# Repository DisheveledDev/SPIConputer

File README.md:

# SPIConputer (working title)

> A retro computer whose system bus is SPI. Every peripheral is an
> autonomous node with its own microcontroller; the main CPU sends it a
> command and the node carries it out without further CPU involvement.

## Status

Design phase. Nothing is built yet. This README is the living design
document: decisions go in the [Decision log](#decision-log), unresolved
items live in [Open questions](#open-questions).

## Concept

- **Bus = SPI.** SCK, MOSI and MISO are shared across all nodes; each
  node gets its own chip-select (SS) line from the main CPU.
- **Autonomous peripherals.** Each node (video, storage, IO, sound,
  console) has its own MCU (ATmega328 or similar). The main CPU issues
  high-level commands ("draw this sprite", "read sector N", "play this
  note") and moves on. Nodes report completion asynchronously.
- **C64 form factor.** The board fits inside a Commodore 64 shell,
  reusing its keyboard and (ideally) its port cutouts.

## Architecture overview

```
                                  +----------------------+
                                  |  MAIN CPU (master)   |
                                  |  MCU: TBD            |
                                  +--+--+--+--+--+--+----+
                                     |  |  |  |  |  |
        Bus: SCK + MOSI + MISO shared; one SS per node; IRQ per node (TBD)
                                     |  |  |  |  |  |
        +----------------------------+  |  |  |  |  +--------------------------+
        |                               |  |  |  |                             |
  +-----+--------+              +-------+  |  |  +-------+             +-------+--------+
  | VIDEO NODE   |              | IO NODE |  |  | STORAGE |             | SOUND NODE     |
  | ATmega2560   |              | ATmega  |  |  | NODE    |             | ATmega328 (TBD)|
  +-----+--------+              +---+-----+  |  +----+----+             +-------+--------+
        |                           |        |       |                         |
  2nd SPI -> Flash           C64 keyboard    |   SD card (SPI)           Audio out (TBD)
  (tile/glyph data)          Joystick x2     |
        |                           |        |
       VGA (DB15)                   |        |
                                    |   +----+--------+
                                    |   | CONSOLE NODE |
                                    |   | RS232 / TBD  |
                                    |   +-------------+
                                    |
                          +---------+---------+
                          | EXPANSION (SDI)   |
                          | bus passthrough   |
                          +-------------------+
```

## System bus

### Signals

| Signal | Direction | Notes |
| ------ | --------- | ----- |
| SCK    | master -> all | Bus clock |
| MOSI   | master -> all | Master out, slave in |
| MISO   | all -> master | Shared; slaves tri-state when not selected |
| SS_n   | master -> one node each | Dedicated chip-select per node |
| IRQ_n  | node -> master | Async completion signal (scheme TBD) |

### Protocol (proposal, unverified)

- Every transaction: master asserts the node's SS, sends a 1-byte
  command, an optional length byte, then payload. The slave responds
  with status byte(s) in the same transfer.
- Each node exposes a small **register map**: writing a command
  register starts an autonomous operation; a status register reports
  idle/busy/done/error; data registers move payloads.
- Completion: node asserts IRQ_n when done (or master polls status).
  See [Open questions](#open-questions).

### Timing and electrical gotchas

- **Slave clock limit:** on classic AVRs, SPI *slave* mode tops out at
  Fosc/4 (4 MHz at 16 MHz Fosc) even though *master* mode can run at
  Fosc/2 (8 MHz). The bus clock is therefore realistically **4 MHz**
  unless a node runs a faster crystal or a different SPI peripheral.
- **Shared MISO:** AVR SPI hardware tri-states MISO while SS is
  deasserted, which is what makes the shared bus work. Firmware must
  keep the SPI peripheral in slave mode; don't reuse MISO as a GPIO
  output.
- **Master SS pin:** in AVR SPI master mode the SS pin must be an
  output (or held high) or the master's own SPI can drop into slave
  mode on a false edge.
- Keep traces short; bus speed is modest but the bus crosses multiple
  boards/connectors.

## Nodes

### Main CPU (master)

- MCU: **TBD**. Candidates: ATmega2560 (fits the all-AVR theme and has
  enough pins for per-node SS + IRQ), or something bigger.
- Owns the bus, dispatches commands, runs the OS/shell/BASIC.
- Needs enough GPIO for: one SS per node, one IRQ per node, any
  console-side RS232 if not handled by a node.

### Video node

- MCU: **ATmega2560-16AU** (specified).
- Output: **VGA via DB15** (rear panel).
- Rendering: **text/sprite system**. Tile map and sprite list live in
  SRAM; tile/glyph bitmaps live in an external **SPI flash** on a
  *second* SPI bus (separate from the system bus).
- Firmware renders scanlines, not a CPU-driven framebuffer.

**Timing budget** (this constrains every video decision):

- Pixel clock comes from an AVR shift register (SPI/USART in master
  mode) = Fosc/2 = **8 MHz** at 16 MHz Fosc.
- One VGA line (31.78 µs) = ~254 pixel clocks at 8 MHz, so visible
  width is roughly **160-250 px** at 1 bit per pixel, packed 8 px per
  byte (~25-30 bytes per line, ~1 µs per byte shifted out).
- Flash reads also max out at ~1 byte/µs (8 MHz SPI). Fetching tile
  data on the fly leaves zero slack, so glyphs/tile rows must be
  **cached into SRAM during blanking** (8 KB SRAM on the 2560).
- Resolutions, colour depth (e.g. 3-bit RGB via 3 pins vs. resistor
  DAC) and sprite count are all [open questions](#open-questions).

### IO node

- MCU: ATmega328 or similar.
- Drives the **C64 keyboard** (8x8 matrix, needs 16 GPIOs + pull-ups)
  via the internal connector, and two **DB9 joystick ports**
  (Atari/C64 standard: 4 directions + fire, active-low, pulled high).
- Scans/debounces locally; the main CPU reads key/joystick *events*,
  not raw matrix state.

### Storage node

- MCU: ATmega328 or similar.
- **SD card in SPI mode** (rear panel slot).
- Exposes block read/write; FAT layer either here or on the main CPU.
- Gotcha: SD cards are **3.3 V logic** — the node needs a 3.3 V rail
  (LDO) and level shifting on MOSI/SCK/SS (MISO can usually feed 5 V
  inputs directly through a divider). Classic AVRs are 5 V parts.

### Console node

- **RS232** serial console (rear panel, DB9).
- Open: true RS232 levels (needs a MAX232-style transceiver) vs. TTL
  serial vs. USB (FTDI/CH340). This node may end up merged into the IO
  node.

### Sound node

- MCU: ATmega328 or similar (TBD).
- Receives note/effect commands and generates audio autonomously;
  output via PWM + RC filter, then amp/jack (TBD).
- Open: chiptune-style synth, sample playback, or a SID-inspired voice
  set.

### Expansion (SDI)

- Rear-panel expansion connector. Intended as a passthrough of the
  system bus (SCK/MOSI/MISO + an SS/IRQ pair + power) so new nodes can
  hang off the bus.
- **"SDI" needs defining** — see [Open questions](#open-questions).

## Connectors

| Connector | Location | Standard / notes |
| --------- | -------- | ---------------- |
| VGA       | rear     | DB15, driven by video node |
| Console   | rear     | DB9 RS232 (or USB) — TBD |
| Expansion | rear     | SDI — bus passthrough, pinout TBD |
| SD card   | rear/side | microSD slot, SPI mode |
| Joystick x2 | rear/side | DB9, Atari/C64 standard |
| Keyboard  | internal | C64 keyboard connector, matrix scan by IO node |
| Power     | rear     | 5 V barrel jack — TBD |

## Form factor

- Board must fit a **C64 shell**; port cutouts should line up with the
  case openings. Open: which C64 revision (breadbin vs. 64C) — they
  have different keyboard connectors and cutouts.

## Power

- Single **5 V** rail for all nodes; local 3.3 V LDO on the storage
  node (and anywhere else 3.3 V logic appears). Total draw is small
  (a handful of AVRs + flash + SD), but budget should be verified once
  nodes are prototyped.

## Firmware conventions (proposed)

- Every node: **command loop** — SPI slave ISR receives command frames,
  main loop executes the current task, sets status, raises IRQ.
- Shared node firmware skeleton/library would avoid re-implementing the
  bus layer per node (TBD once toolchain is chosen).
- Each board exposes an **ICSP/ISP header** for initial programming
  and bootloader flashing.

## Development tooling

TBD. Candidates: avr-gcc + avrdude directly, PlatformIO, or Arduino
CLI. Decide in the [Decision log](#decision-log) and document the
canonical build/flash commands here once real code exists.

## Decision log

| # | Decision | Rationale | Date |
| - | -------- | --------- | ---- |
|   | *(none yet)* |  |  |

## Open questions

1. **Main CPU** — which MCU drives the bus and runs the OS?
2. **Bus protocol** — exact command framing; register-map layout per
   node; IRQ scheme (one line per node vs. shared open-collector).
3. **Video modes** — target resolution(s), colour depth, sprite count,
   tile cache strategy within the 8 MHz pixel-clock budget.
4. **SDI definition** — what exactly does the expansion connector
   carry, and what can plug into it?
5. **Sound architecture** — synth vs. samples, voice count, output
   stage (amp, jack on case?).
6. **Console** — true RS232 levels, TTL, or USB?
7. **C64 case revision** — breadbin or 64C (keyboard connector,
   cutouts, mounting holes differ).
8. **Toolchain** — avr-gcc / PlatformIO / Arduino, and the flash
   workflow for each node.
9. **Firmware framework** — shared bus-layer library across nodes, or
   per-node implementations?

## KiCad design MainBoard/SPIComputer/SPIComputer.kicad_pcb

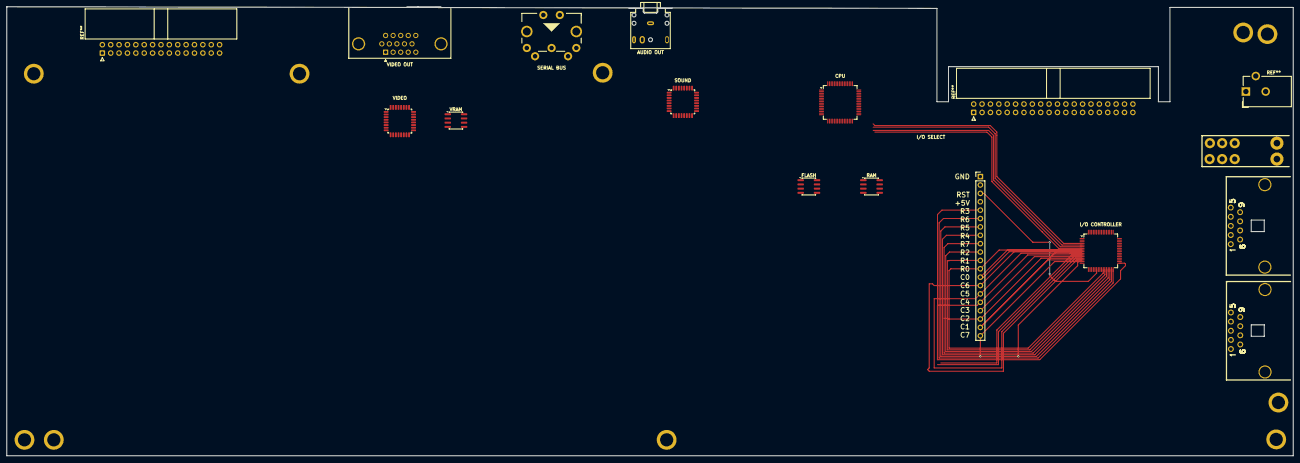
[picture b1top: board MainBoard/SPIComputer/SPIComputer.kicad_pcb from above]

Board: 2 copper layers, 390.0 x 136.1 mm, 14 parts (0 on the bottom side), 2 nets.

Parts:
AUDIO OUT: Jack_3.5mm; Jack_3.5mm_CUI_SJ1-3524N_Horizontal
CN8, CN9: JOYPORT_DB9
CPU: AVR128DB64-I-PT
FLASH: SOIC-8_3.9x4.9mm_P1.27mm
HOLE4: (no value)
I/O CONTROLLER: AVR128DB64-I-PT
RAM: SOIC-8_3.9x4.9mm_P1.27mm
SERIAL BUS: DIN5_MIDI
SOUND: AVR128DA32-I-PT
SW1: POWER_SWITCH
VIDEO: AVR128DA32-I-PT
VIDEO OUT: DSUB-15-HD_Socket_Horizontal_P2.29x2.54mm_EdgePin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; DSUB-15-HD_Socket_Horizontal_P2.29x2.54mm_EdgePinOffset8.35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
VRAM: SOIC-8_3.9x4.9mm_P1.27mm

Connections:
+5V: CN8.7, CN9.7, SW1.4
GND: CN8.8, CN9.8, HOLE4.1, SW1.pe (SHIELD)

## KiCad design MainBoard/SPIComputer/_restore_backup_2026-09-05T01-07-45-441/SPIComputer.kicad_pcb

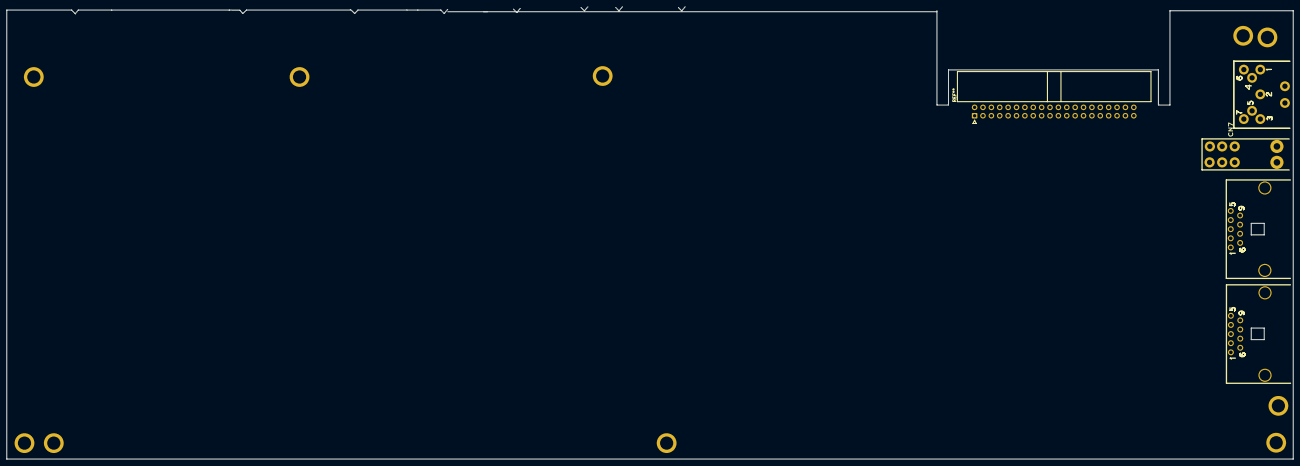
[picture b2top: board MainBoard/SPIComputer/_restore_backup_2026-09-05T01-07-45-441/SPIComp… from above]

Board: 2 copper layers, 390.0 x 137.1 mm, 5 parts (0 on the bottom side), 4 nets, no tracks yet.

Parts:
CN7: POWER_CON_D7_250407
CN8, CN9: JOYPORT_DB9
HOLE4: (no value)
SW1: POWER_SWITCH

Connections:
+5V: CN8.7, CN9.7, SW1.4
/+5V': CN7.4, CN7.5
/GND': CN7.1, CN7.2, CN7.3
GND: CN7.pe (shield), CN8.8, CN9.8, HOLE4.1, SW1.pe (SHIELD)
